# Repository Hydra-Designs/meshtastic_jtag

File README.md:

# meshtastic_jtag
An easy to assemble JTAG debugging PCB for meshtastic

## Features
- Works with any ESP32 Devkit C compatible board  
- Support for OLED (front) and GPS (back)  
- Compatible with ebyte e22-900m22s LORA module  
- Built in 915MHz monopole antenna   

## Project status
- Gerbers are not tested and schematic has not been reviewed  
- Antenna matching network needs to be optimized  

## Assembly instructions
- Gerber files are in the /gerber/ directory, they are plotted in a format that can be directly uploaded to JLPCB    
- When ordering from JLCPCB don't forget to tick "specify a location" under "remove order number" so that the JLC PCB number is at the PCB back side  
- Assembly should be pretty self-explanatory, minimum hardware requirement is the ESP32 Devkit and the e22-900m22s LORA module with the two decoupling capacitors  
- OLED display goes on the PCB front side  
- NEO6M GPS module goes on the PCB back side  
- The matching network needs fine tuning, for now you should not place C3 and C4 and add a short in place of L1 (small blob of solder)  

## Contributing

Please contribute using [Github Flow](https://guides.github.com/introduction/flow/). Create a branch, add commits, and [open a pull request](https://github.com/PlumRugOfDoom/project-hydra-meshtastic-pcb/compare/). Remember to ```git clone --recursive git@github.com:Hydra-Designs/meshtastic_jtag.git``` or ```git submodule update --init``` since the official espressif KiCAD libs have been included in a submodule.  

## Support

Please [open an issue](https://github.com/PlumRugOfDoom/project-hydra-meshtastic-pcb/issues/new) for support.

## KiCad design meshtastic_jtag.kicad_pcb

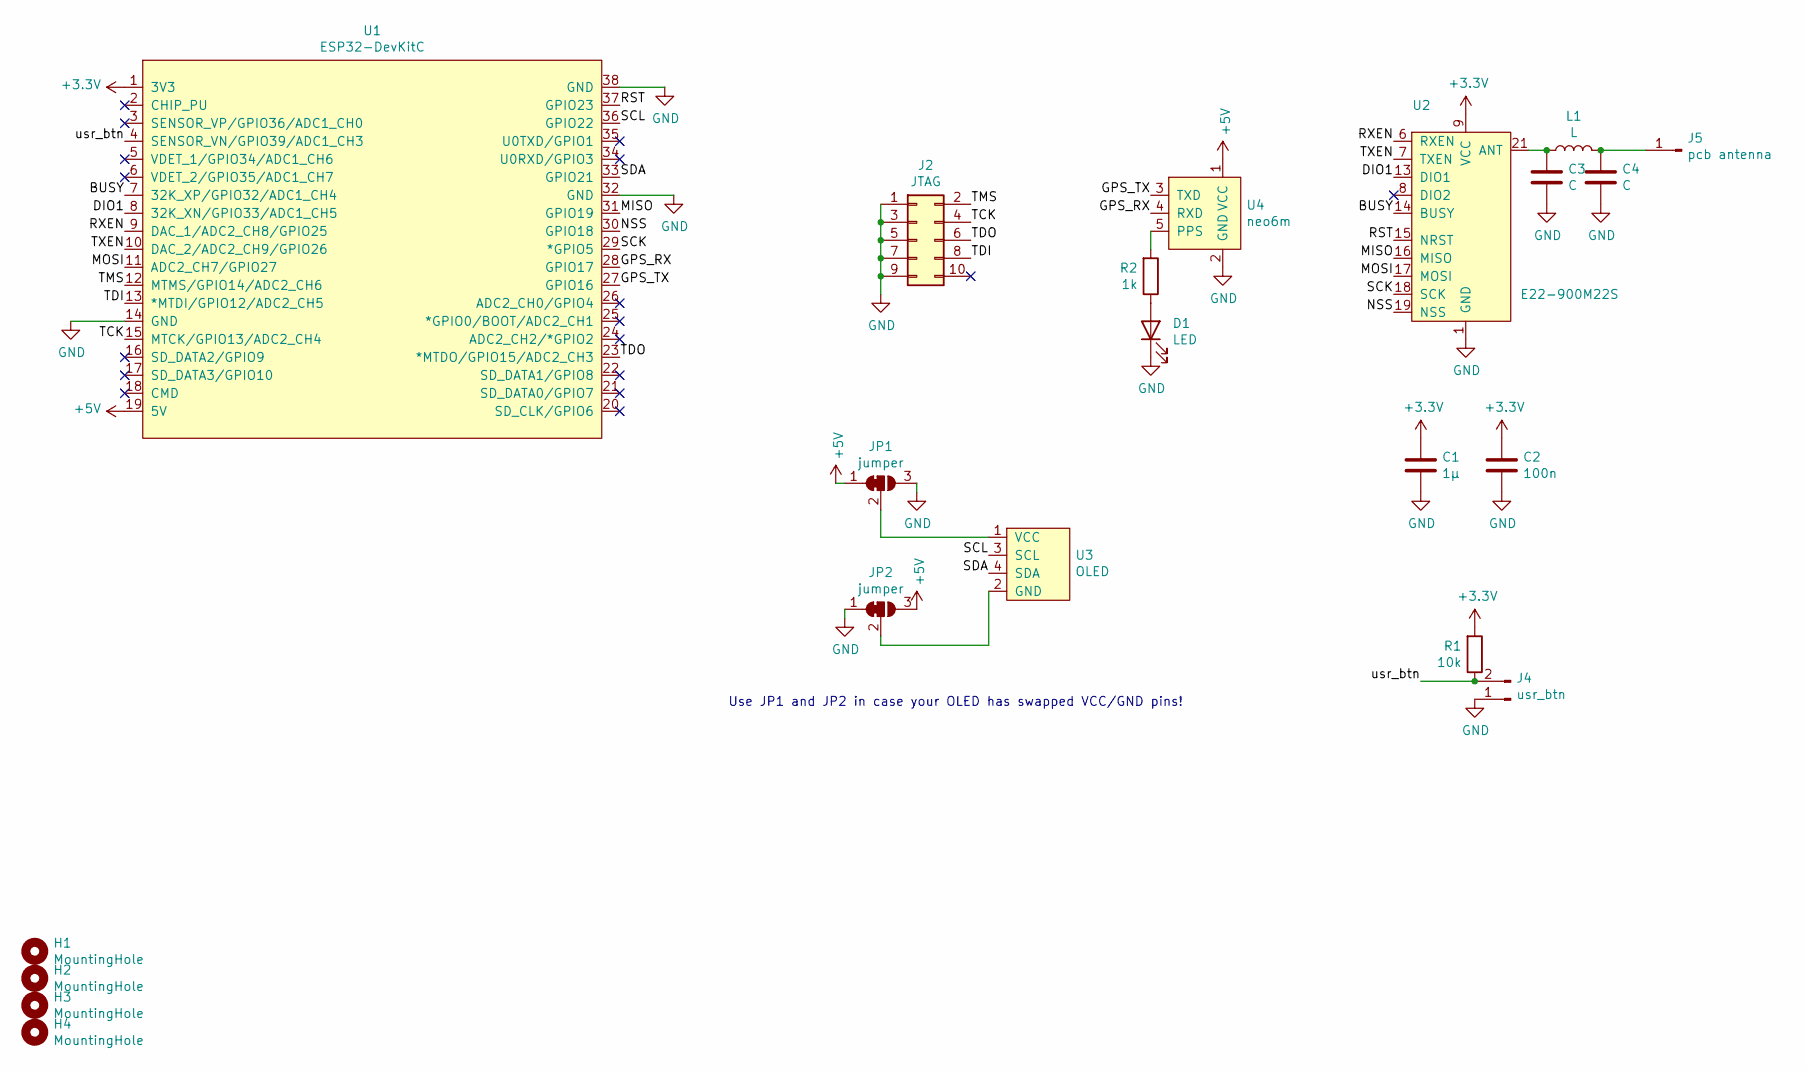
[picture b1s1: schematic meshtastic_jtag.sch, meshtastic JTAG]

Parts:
C1: 1µ; C_0603_1608Metric
C2: 100n; C_0603_1608Metric
C3, C4: C; C_0402_1005Metric
D1: LED; LED_0805_2012Metric
H1, H2, H3, H4: MountingHole; MountingHole_3.2mm_M3_DIN965
J2: JTAG; PinHeader_2x05_P2.54mm_Vertical
J4: usr_btn; PinHeader_1x02_P2.54mm_Vertical
J5: pcb antenna; TI_DN024
JP1, JP2: jumper; SolderJumper-3_P1.3mm_Bridged12_Pad1.0x1.5mm_NumberLabels
L1: L; C_0402_1005Metric
R1: 10k; R_0805_2012Metric
R2: 1k; R_0805_2012Metric
U1: ESP32-DevKitC
U2: E22-900M22S; e22-900m22s
U3: OLED; oled
U4: neo6m

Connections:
+3V3: C1.1, C2.1, R1.2, U1.1 (3V3), U2.9 (VCC)
+5V: JP1.1 (A), JP2.3 (B), U1.19 (5V), U4.1 (VCC)
/BUSY: U1.7 (32K_XP/GPIO32/ADC1_CH4), U2.14 (BUSY)
/DIO1: U1.8 (32K_XN/GPIO33/ADC1_CH5), U2.13 (DIO1)
/GPS_RX: U1.28 (GPIO17), U4.4 (RXD)
/GPS_TX: U1.27 (GPIO16), U4.3 (TXD)
/MISO: U1.31 (GPIO19), U2.16 (MISO)
/MOSI: U1.11 (ADC2_CH7/GPIO27), U2.17 (MOSI)
/NSS: U1.30 (GPIO18), U2.19 (NSS)
/RST: U1.37 (GPIO23), U2.15 (NRST)
/RXEN: U1.9 (DAC_1/ADC2_CH8/GPIO25), U2.6 (RXEN)
/SCK: U1.29 (*GPIO5), U2.18 (SCK)
/SCL: U1.36 (GPIO22), U3.3 (SCL)
/SDA: U1.33 (GPIO21), U3.4 (SDA)
/TCK: J2.4, U1.15 (MTCK/GPIO13/ADC2_CH4)
/TDI: J2.8, U1.13 (*MTDI/GPIO12/ADC2_CH5)
/TDO: J2.6, U1.23 (*MTDO/GPIO15/ADC2_CH3)
/TMS: J2.2, U1.12 (MTMS/GPIO14/ADC2_CH6)
/TXEN: U1.10 (DAC_2/ADC2_CH9/GPIO26), U2.7 (TXEN)
/usr_btn: J4.2, R1.1, U1.4 (SENSOR_VN/GPIO39/ADC1_CH3)
GND: C1.2, C2.2, C3.2, C4.2, D1.1 (K), J2.1, J2.3, J2.5, J2.7, J2.9, J4.1, JP1.3 (B), JP2.1 (A), U1.14 (GND), U1.32 (GND), U1.38 (GND), U2.1 (GND), U2.2 (GND), U2.3 (GND), U2.4 (GND), U2.5 (GND), U2.10 (GND), U2.11 (GND), U2.12 (GND), U2.20 (GND), U2.22 (GND), U4.2 (GND)
unnamed: C3.1, L1.1, U2.21 (ANT)
unnamed: C4.1, J5.1, L1.2
unnamed: D1.2 (A), R2.1
unnamed: JP1.2 (C), U3.1 (VCC)
unnamed: JP2.2 (C), U3.2 (GND)
unnamed: R2.2, U4.5 (PPS)

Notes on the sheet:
Use JP1 and JP2 in case your OLED has swapped VCC/GND pins!

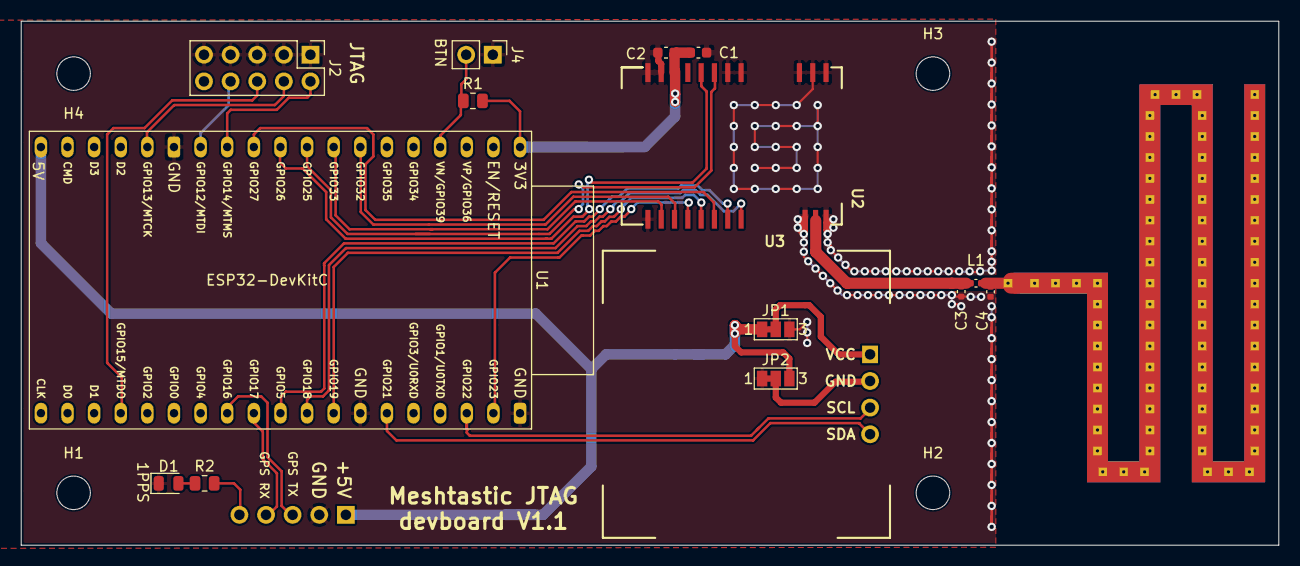
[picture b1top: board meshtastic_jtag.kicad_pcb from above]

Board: 2 copper layers, 120.0 x 50.0 mm, 21 parts (1 on the bottom side), 27 nets.

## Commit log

2021-12-29 schematic pdf and gerbers added
2021-12-30 bump to V1.1, solder jumpers to swap OLED VCC/GND added
